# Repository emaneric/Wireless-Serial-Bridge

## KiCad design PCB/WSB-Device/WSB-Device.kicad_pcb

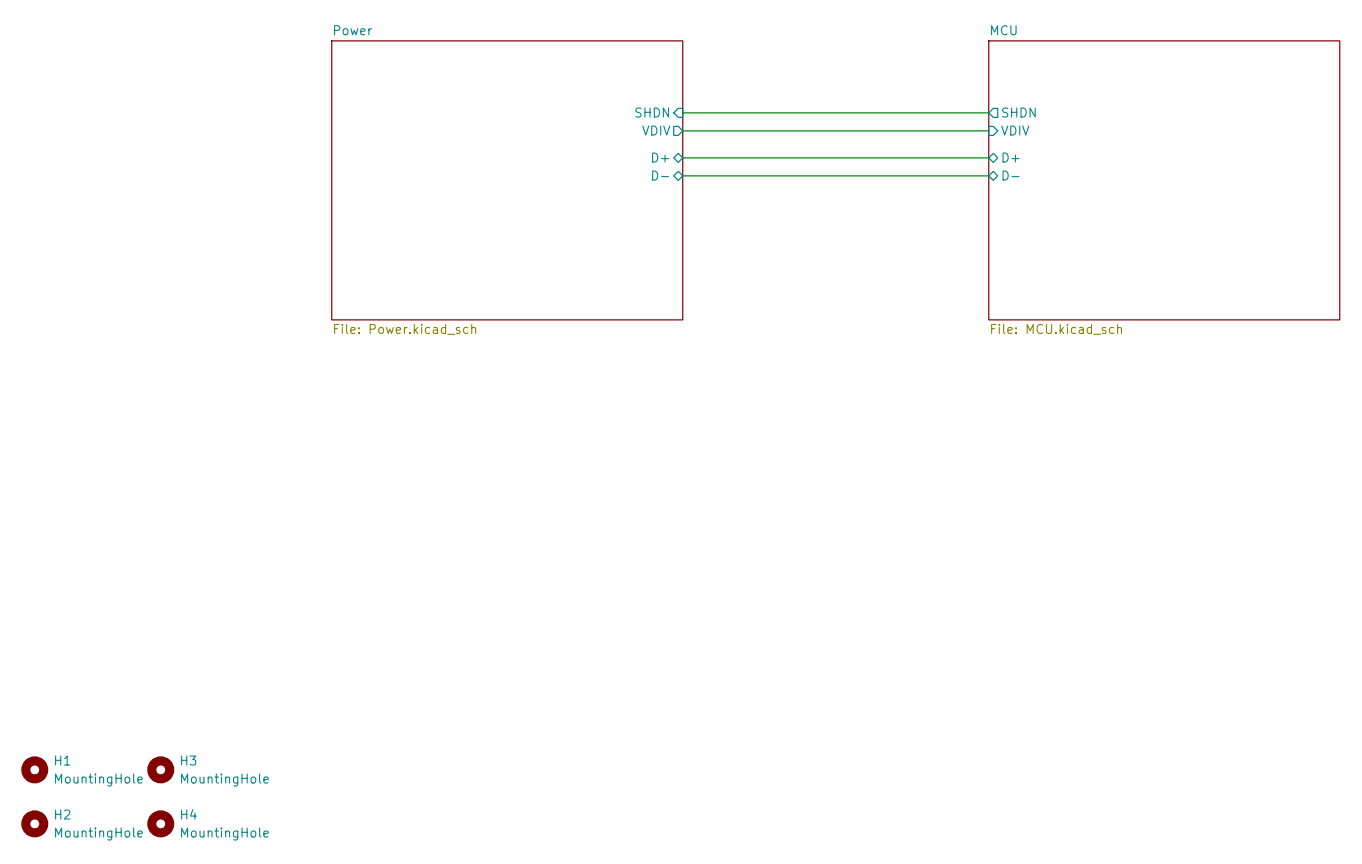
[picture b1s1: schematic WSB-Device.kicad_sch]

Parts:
H1, H2, H3, H4: MountingHole; MountingHole_2.2mm_M2

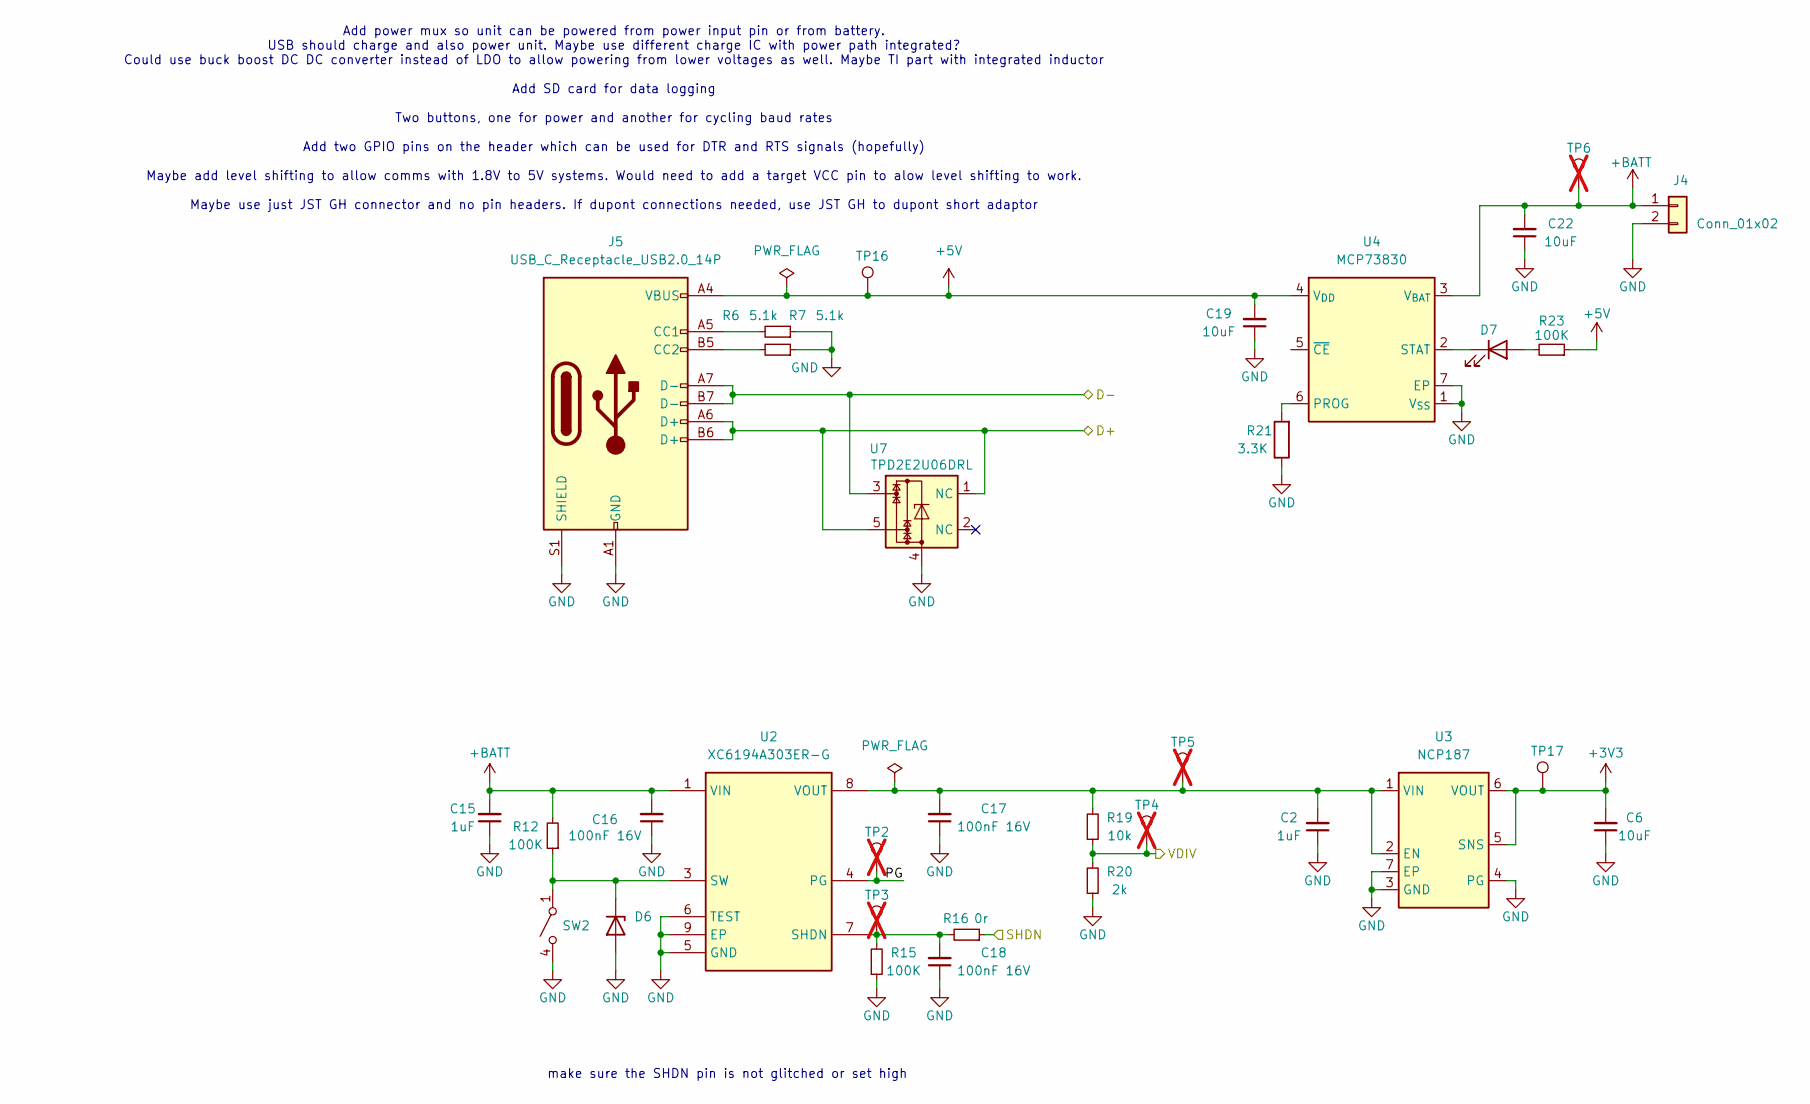
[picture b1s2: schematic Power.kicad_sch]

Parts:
C2: 1uF; C_0402_1005Metric; Voltage 10V
C6, C19, C22: 10uF; C_0603_1608Metric; Voltage 10V
C15: 1uF; C_0603_1608Metric; Voltage 10V
C16, C17, C18: 100nF 16V; C_0402_1005Metric
D6: D_Zener; D_SOD-323
D7: LED; LED_0603_1608Metric
J4: Conn_01x02; JST_PH_S2B-PH-SM4-TB_1x02-1MP_P2.00mm_Horizontal
J5: USB_C_Receptacle_USB2.0_14P; USB_C_Receptacle_G-Switch_GT-USB-7010ASV
R6, R7: 5.1k; R_0201_0603Metric
R12, R15, R23: 100K; R_0402_1005Metric
R16: 0r; R_0402_1005Metric
R19: 10k; R_0402_1005Metric
R20: 2k; R_0402_1005Metric
R21: 3.3K; R_0402_1005Metric
SW2: SW_SPST_4_PIN; 1TS026A-2300-0553-CT
TP2, TP3, TP4, TP5, TP6: TestPoint; TestPoint_Pad_D1.0mm; not fitted
TP16, TP17: TestPoint; TestPoint_Pad_D1.0mm
U2: XC6194A303ER-G; XC6194_USP-8B06
U3: NCP187; OnSemi_WDFN6_2x2_0.65P_CASE_511BR
U4: MCP73830; TDFN-6-1EP_2x2mm_P0.5mm_EP1.6x0.6mm_ThermalVias
U7: TPD2E2U06DRL; SOT-553

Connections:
+3V3: C6.2, TP17.1, U3.5 (SNS), U3.6 (VOUT); also elsewhere on the board
+5V: C19.2, J5.A4 (VBUS), J5.A9 (VBUS), J5.B4 (VBUS), J5.B9 (VBUS), R23.1, TP16.1, U4.4 (V_{DD}); also elsewhere on the board
+BATT: C15.2, C16.2, C22.2, J4.1, R12.2, TP6.1, U2.1 (VIN), U4.3 (V_{BAT})
/MCU/D+: J5.A6 (D+), J5.B6 (D+), U7.1 (NC), U7.5; also elsewhere on the board
/MCU/D-: J5.A7 (D-), J5.B7 (D-), U7.3; also elsewhere on the board
/MCU/SHDN: R16.1; also elsewhere on the board
/MCU/VDIV: R19.1, R20.2, TP4.1; also elsewhere on the board
/Power/PG: TP2.1, U2.4 (PG)
GND: C2.1, C6.1, C15.1, C16.1, C17.1, C18.1, C19.1, C22.1, D6.2 (A), J4.2, J5.A1 (GND), J5.A12 (GND), J5.B1 (GND), J5.B12 (GND), J5.S1 (SHIELD), R6.1, R7.1, R15.1, R20.1, R21.1, SW2.3 (B), SW2.4 (B), U2.5 (GND), U2.6 (TEST), U2.9 (EP), U3.3 (GND), U3.4 (PG), U3.7 (EP), U4.1 (V_{SS}), U4.7 (EP), U7.4; also elsewhere on the board
unnamed: D6.1 (K), R12.1, SW2.1 (A), SW2.2 (A), U2.3 (SW)
unnamed: D7.2 (A), R23.2
unnamed: D7.1 (K), U4.2 (STAT)
unnamed: J5.A5 (CC1), R6.2
unnamed: J5.B5 (CC2), R7.2
unnamed: C18.2, R15.2, R16.2, TP3.1, U2.7 (SHDN)
unnamed: C2.2, C17.2, R19.2, TP5.1, U2.8 (VOUT), U3.1 (VIN), U3.2 (EN)
unnamed: R21.2, U4.6 (PROG)

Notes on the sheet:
Add power mux so unit can be powered from power input pin or from battery. USB should charge and also power unit. Maybe use different charge IC with power path integrated? Could use buck boost DC DC converter instead of LDO to allow powering from lower voltages as well. Maybe TI part with integrate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
make sure the SHDN pin is not glitched or set high

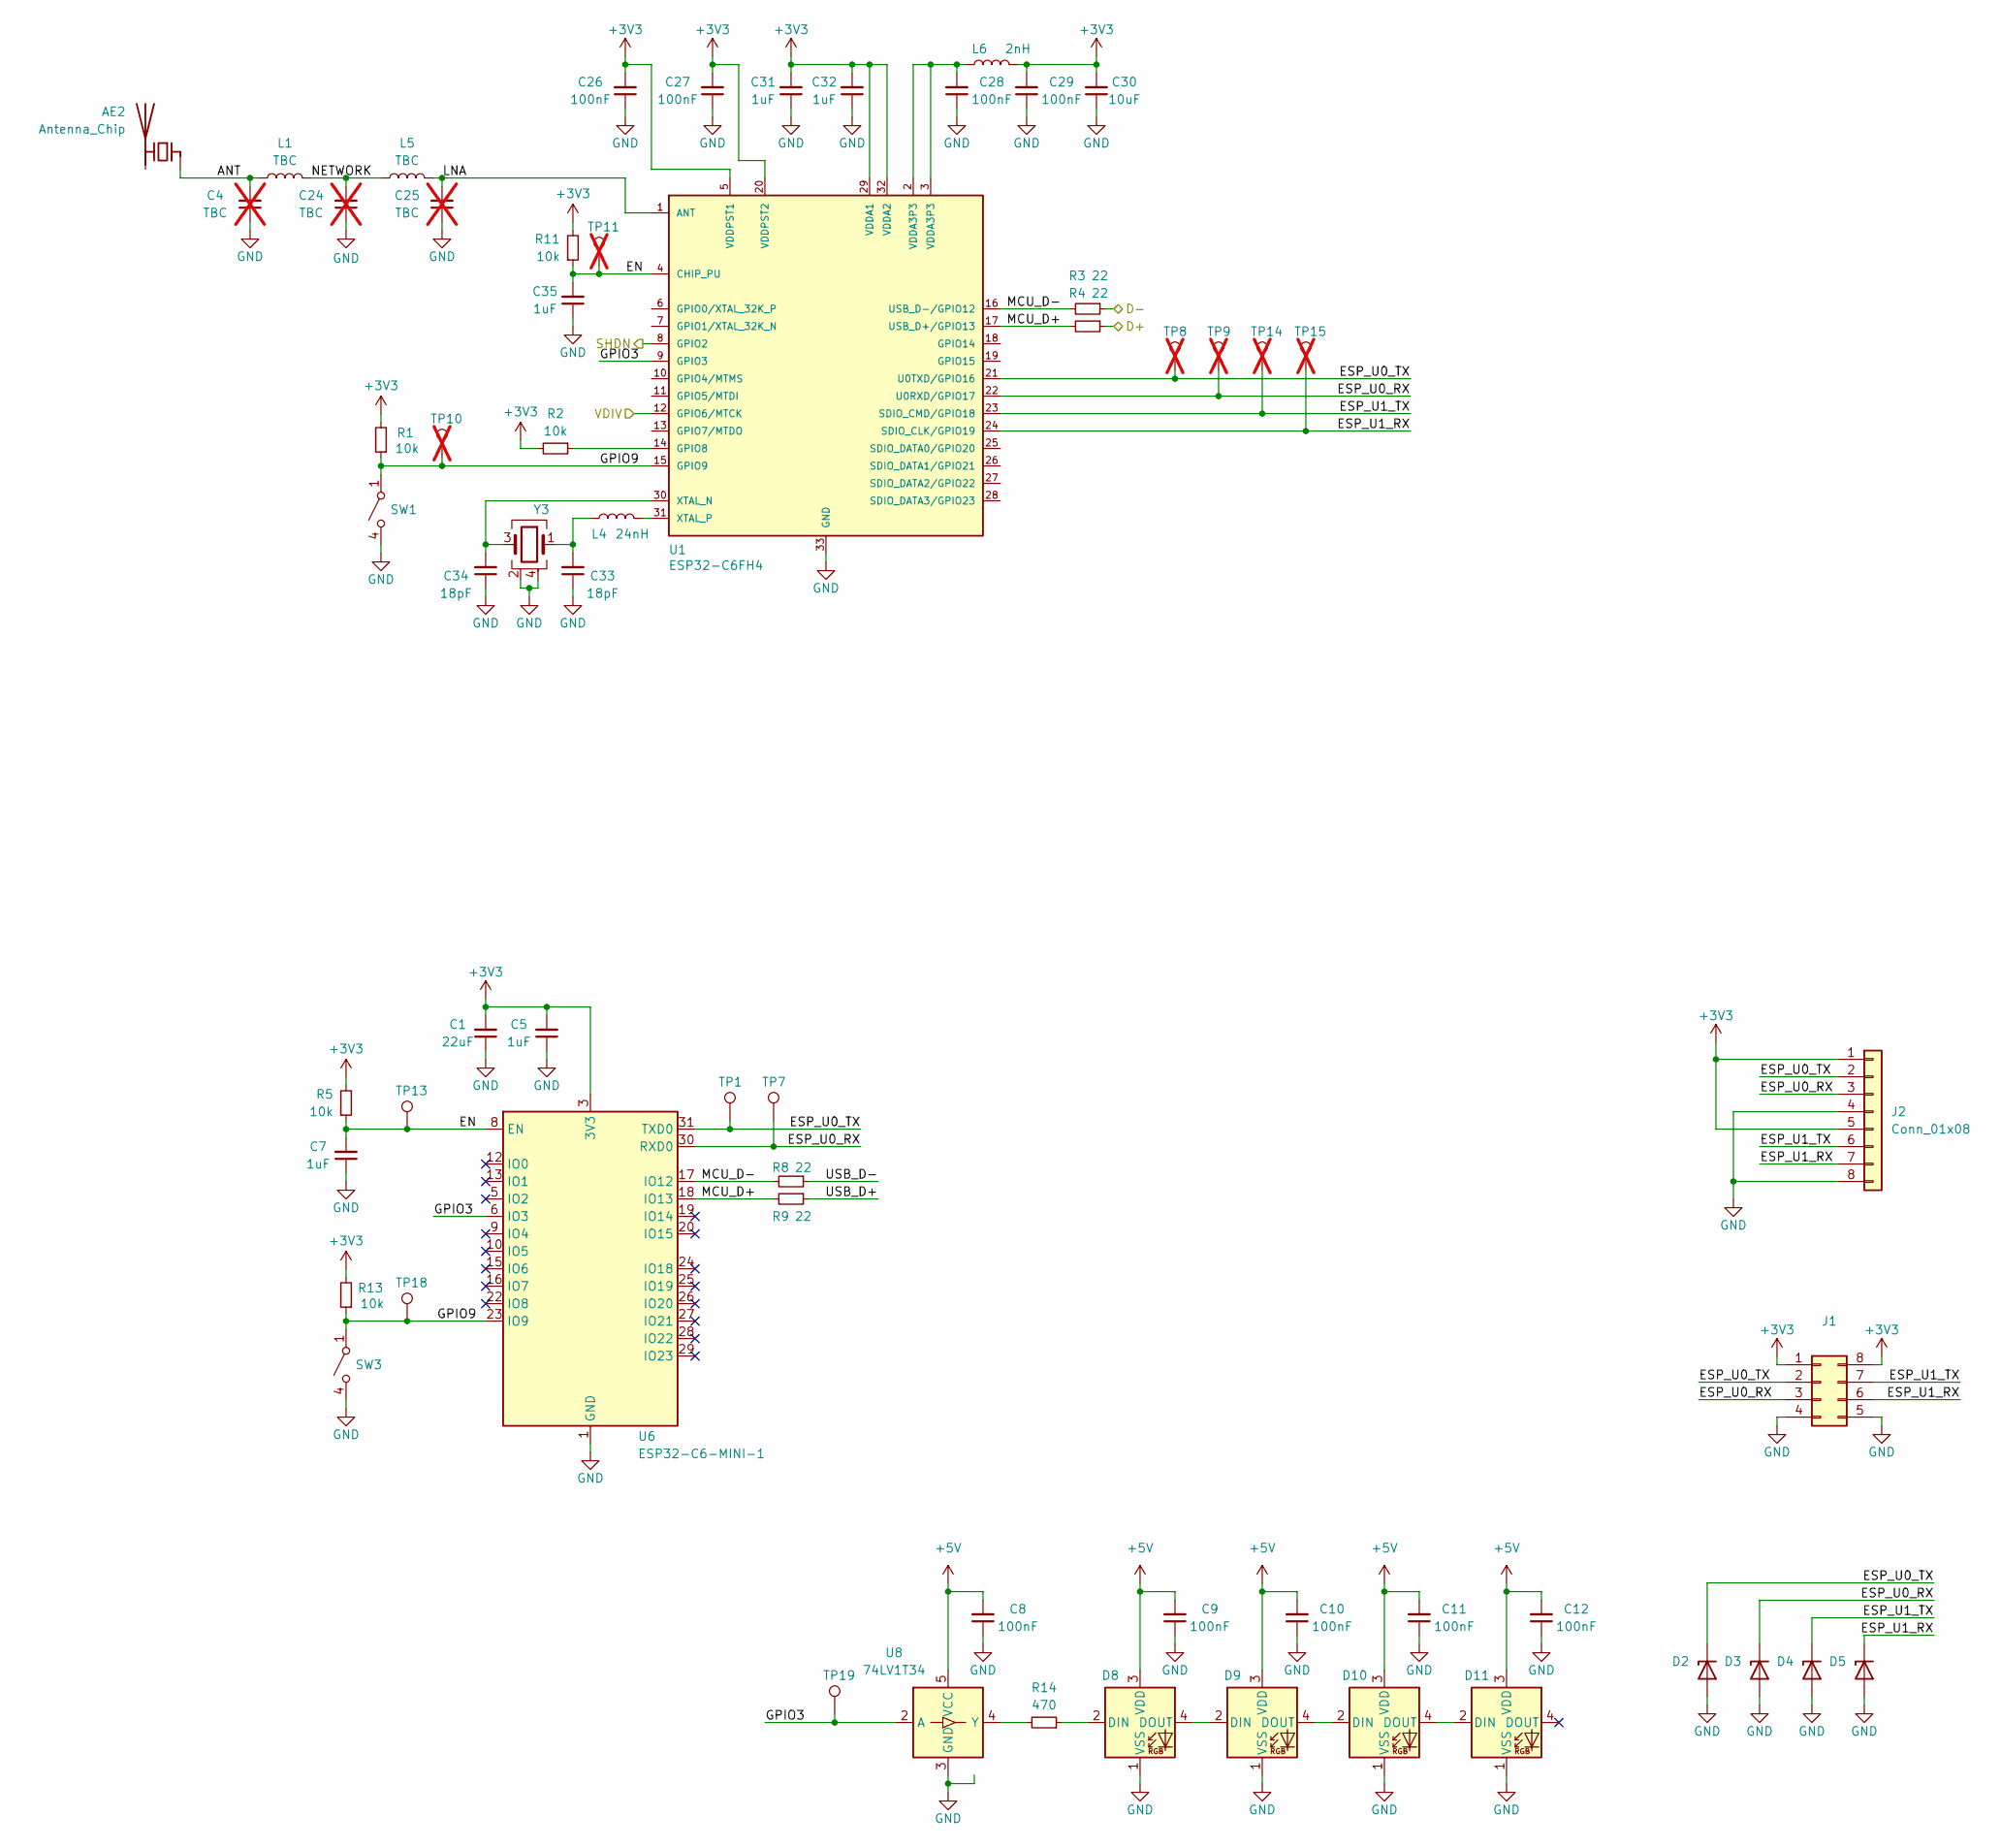
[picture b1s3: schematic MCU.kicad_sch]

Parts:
AE2: Antenna_Chip; ANT3216LL00R2400A
C1: 22uF; C_0603_1608Metric; Voltage 10V
C4, C24, C25: TBC; C_0402_1005Metric; not fitted
C5, C7, C31, C32, C35: 1uF; C_0402_1005Metric; Voltage 10V
C8, C9, C10, C11, C12: 100nF; C_0201_0603Metric; Voltage 10V
C26, C27, C28, C29: 100nF; C_0402_1005Metric; Voltage 10V
C30: 10uF; C_0603_1608Metric; Voltage 10V
C33, C34: 18pF; C_0402_1005Metric; Voltage 10V
D2, D3, D4, D5: ESD7351XV2T1G; D_SOD-323
D8, D9, D10, D11: XL-3210RGBC-2812B
J1: Conn_02x04_Counter_Clockwise; PinHeader_2x04_P2.54mm_Horizontal
J2: Conn_01x08; JST_GH_SM08B-GHS-TB_1x08-1MP_P1.25mm_Horizontal
L1, L5: TBC; L_0402_1005Metric
L4: 24nH; L_0402_1005Metric
L6: 2nH; L_0402_1005Metric
R1, R2, R11: 10k; R_0402_1005Metric
R3, R4: 22; R_0402_1005Metric
R5, R13: 10k; R_0201_0603Metric
R8, R9: 22; R_0201_0603Metric
R14: 470; R_0201_0603Metric
SW1, SW3: SW_SPST_4_PIN; 1TS026A-2300-0553-CT
TP1, TP7, TP13, TP18, TP19: TestPoint; TestPoint_Pad_D1.0mm
TP8, TP9, TP10, TP11, TP14, TP15: TestPoint; TestPoint_Pad_D1.0mm; not fitted
U1: ESP32-C6FH4; QFN-32-1EP_5x5mm_P0.5mm_EP3.7x3.7mm_ThermalVias; PARTREV v0.5
U6: ESP32-C6-MINI-1
U8: 74LV1T34; X2SON5_0.8x0.8mm_SOT1226
Y3: Crystal_GND24; Crystal_SMD_2520-4Pin_2.5x2.0mm

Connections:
+3V3: C1.2, C5.2, C26.2, C27.2, C29.2, C30.2, C31.2, C32.2, J1.1, J1.8, J2.1, J2.5, L6.2, R1.2, R2.2, R5.2, R11.2, R13.2, U1.5 (VDDPST1), U1.20 (VDDPST2), U1.29 (VDDA1), U1.32 (VDDA2), U6.3 (3V3); also elsewhere on the board
+5V: C8.2, C9.2, C10.2, C11.2, C12.2, D8.3 (VDD), D9.3 (VDD), D10.3 (VDD), D11.3 (VDD), U8.5 (VCC); also elsewhere on the board
/MCU/ANT: AE2.1 (FEED), C4.2, L1.1
/MCU/D+: R4.1; also elsewhere on the board
/MCU/D-: R3.1; also elsewhere on the board
/MCU/EN: C7.2, C35.2, R5.1, R11.1, TP11.1, TP13.1, U1.4 (CHIP_PU), U6.8 (EN)
/MCU/ESP_U0_RX: D3.1 (K), J1.3, J2.3, TP7.1, TP9.1, U1.22 (U0RXD/GPIO17), U6.30 (RXD0)
/MCU/ESP_U0_TX: D2.1 (K), J1.2, J2.2, TP1.1, TP8.1, U1.21 (U0TXD/GPIO16), U6.31 (TXD0)
/MCU/ESP_U1_RX: D5.1 (K), J1.6, J2.7, TP15.1, U1.24 (SDIO_CLK/GPIO19)
/MCU/ESP_U1_TX: D4.1 (K), J1.7, J2.6, TP14.1, U1.23 (SDIO_CMD/GPIO18)
/MCU/GPIO3: TP19.1, U1.9 (GPIO3), U6.6 (IO3), U8.2 (A)
/MCU/GPIO9: R1.1, R13.1, SW1.1 (A), SW1.2 (A), SW3.1 (A), SW3.2 (A), TP10.1, TP18.1, U1.15 (GPIO9), U6.23 (IO9)
/MCU/LNA: C25.2, L5.2, U1.1 (ANT)
/MCU/MCU_D+: R4.2, R9.2, U1.17 (USB_D+/GPIO13), U6.18 (IO13)
/MCU/MCU_D-: R3.2, R8.2, U1.16 (USB_D-/GPIO12), U6.17 (IO12)
/MCU/NETWORK: C24.2, L1.2, L5.1
/MCU/SHDN: U1.8 (GPIO2); also elsewhere on the board
/MCU/USB_D+: R9.1
/MCU/USB_D-: R8.1
/MCU/VDIV: U1.12 (GPIO6/MTCK); also elsewhere on the board
GND: C1.1, C4.1, C5.1, C7.1, C8.1, C9.1, C10.1, C11.1, C12.1, C24.1, C25.1, C26.1, C27.1, C28.1, C29.1, C30.1, C31.1, C32.1, C33.1, C34.1, C35.1, D2.2 (A), D3.2 (A), D4.2 (A), D5.2 (A), D8.1 (VSS), D9.1 (VSS), D10.1 (VSS), D11.1 (VSS), J1.4, J1.5, J2.4, J2.8, SW1.3 (B), SW1.4 (B), SW3.3 (B), SW3.4 (B), U1.33 (GND), U6.1 (GND), U6.2 (GND), U6.11 (GND), U6.14 (GND), U6.36 (GND), U6.37 (GND), U6.38 (GND), U6.39 (GND), U6.40 (GND), U6.41 (GND), U6.42 (GND), U6.43 (GND), U6.44 (GND), U6.45 (GND), U6.46 (GND), U6.47 (GND), U6.48 (GND), U6.49 (GND), U6.50 (GND), U6.51 (GND), U6.52 (GND), U6.53 (GND), U8.3 (GND), Y3.2, Y3.4; also elsewhere on the board
unnamed: C28.2, L6.1, U1.2 (VDDA3P3), U1.3 (VDDA3P3)
unnamed: C33.2, L4.2, Y3.1
unnamed: D8.2 (DIN), R14.1
unnamed: D8.4 (DOUT), D9.2 (DIN)
unnamed: D9.4 (DOUT), D10.2 (DIN)
unnamed: D10.4 (DOUT), D11.2 (DIN)
unnamed: R2.1, U1.14 (GPIO8)
unnamed: C34.2, U1.30 (XTAL_N), Y3.3
unnamed: L4.1, U1.31 (XTAL_P)
unnamed: R14.2, U8.4 (Y)

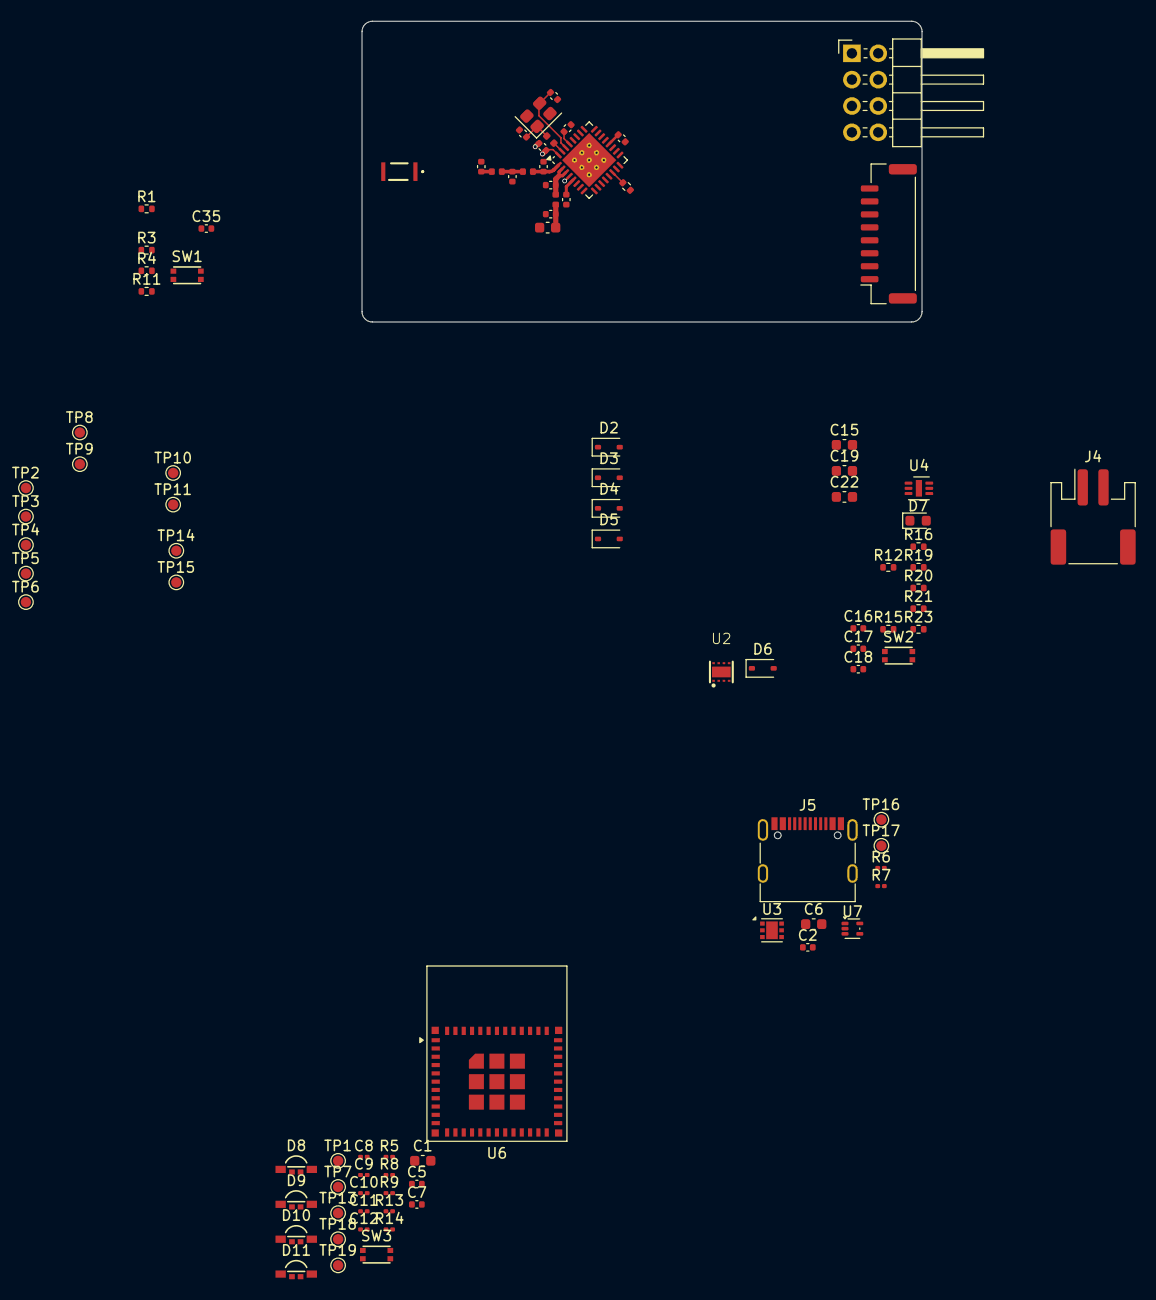
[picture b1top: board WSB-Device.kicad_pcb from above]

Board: 4 copper layers, 54.0 x 29.0 mm, 99 parts (0 on the bottom side), 38 nets.

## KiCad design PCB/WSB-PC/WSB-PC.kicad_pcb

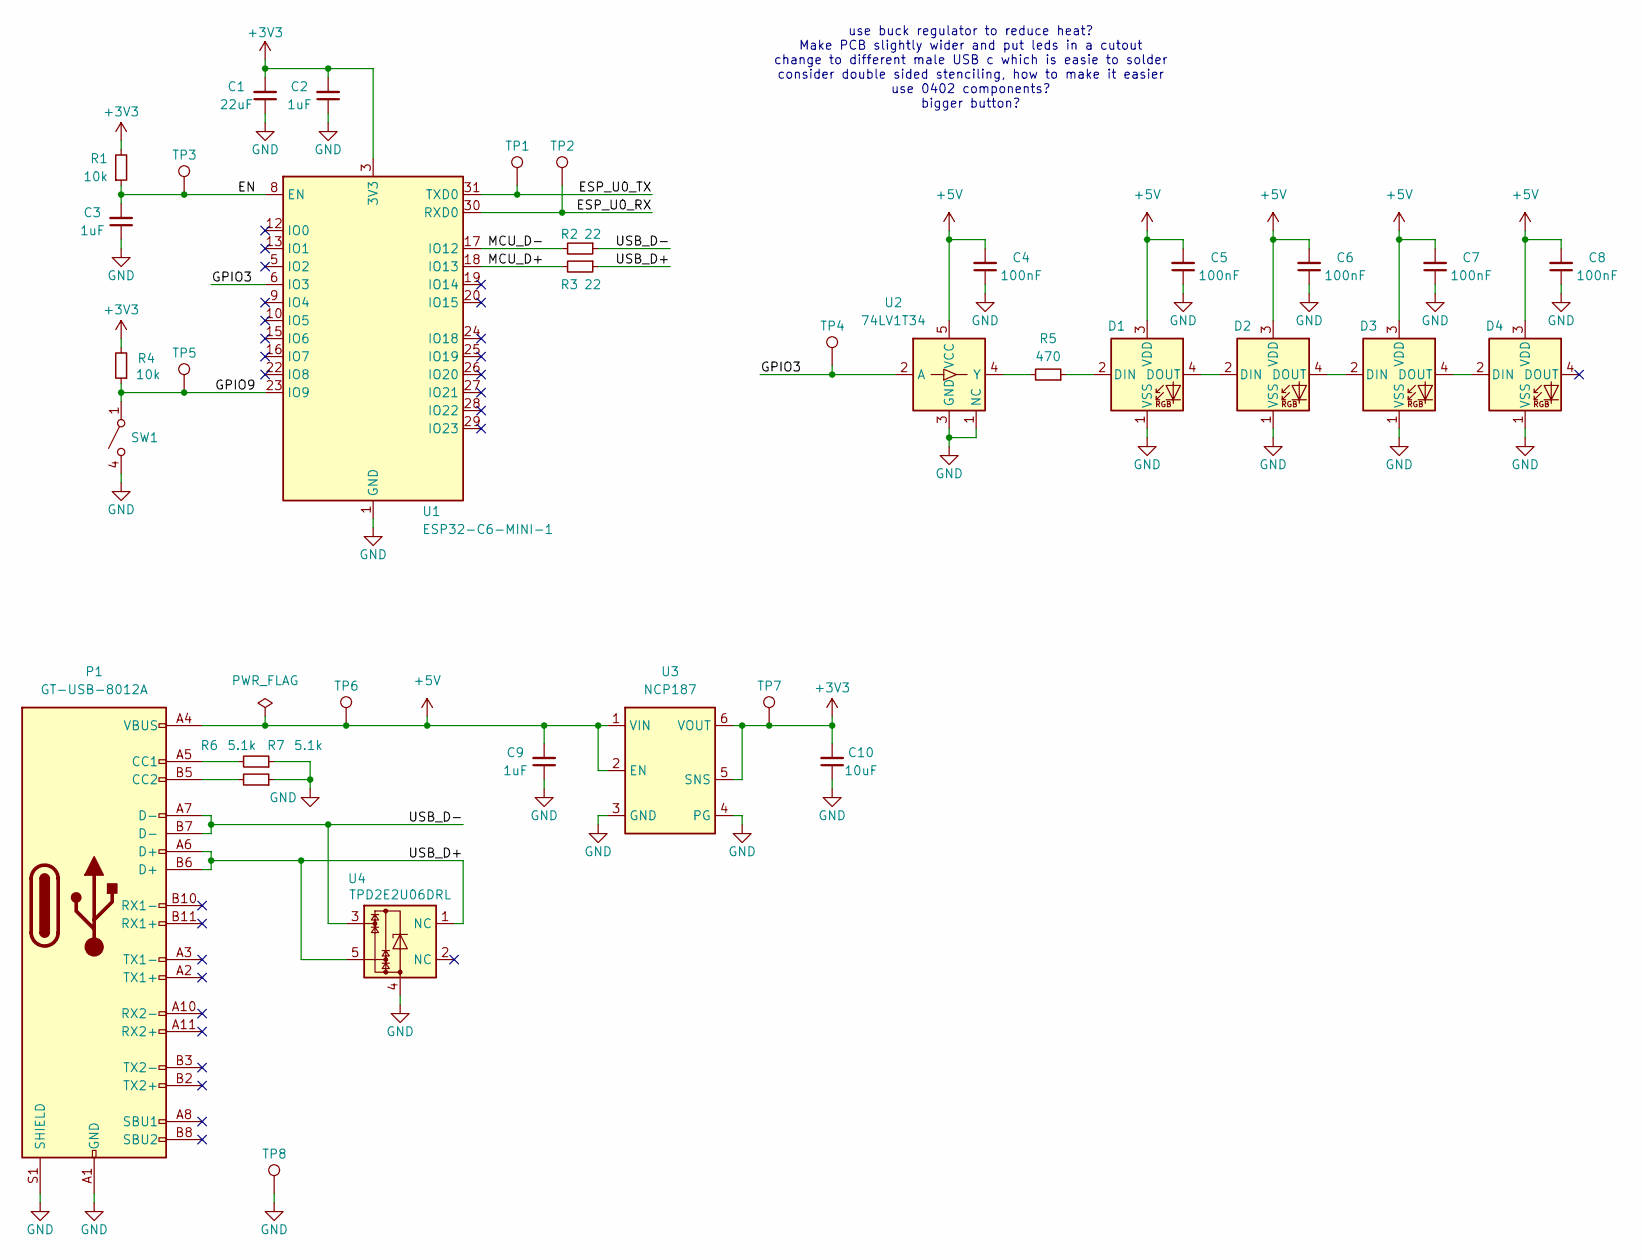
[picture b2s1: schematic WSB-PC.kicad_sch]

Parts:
C1: 22uF; C_0603_1608Metric; Voltage 10V
C2, C3, C9: 1uF; C_0402_1005Metric; Voltage 10V
C4, C5, C6, C7, C8: 100nF; C_0201_0603Metric; Voltage 10V
C10: 10uF; C_0603_1608Metric; Voltage 10V
D1, D2, D3, D4: XL-3210RGBC-2812B
P1: GT-USB-8012A
R1, R4: 10k; R_0201_0603Metric
R2, R3: 22; R_0201_0603Metric
R5: 470; R_0201_0603Metric
R6, R7: 5.1k; R_0201_0603Metric
SW1: SW_SPST_4_PIN; 1TS026A-2300-0553-CT
TP1, TP2, TP3, TP4, TP5, TP6, TP7, TP8: TestPoint; TestPoint_Pad_D1.0mm
U1: ESP32-C6-MINI-1
U2: 74LV1T34; X2SON5_0.8x0.8mm_SOT1226
U3: NCP187; OnSemi_WDFN6_2x2_0.65P_CASE_511BR
U4: TPD2E2U06DRL; SOT-553

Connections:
+3V3: C1.2, C2.2, C10.2, R1.2, R4.2, TP7.1, U1.3 (3V3), U3.5 (SNS), U3.6 (VOUT)
+5V: C4.2, C5.2, C6.2, C7.2, C8.2, C9.2, D1.3 (VDD), D2.3 (VDD), D3.3 (VDD), D4.3 (VDD), P1.A4 (VBUS), P1.A9 (VBUS), P1.B4 (VBUS), P1.B9 (VBUS), TP6.1, U2.5 (VCC), U3.1 (VIN), U3.2 (EN)
/EN: C3.2, R1.1, TP3.1, U1.8 (EN)
/ESP_U0_RX: TP2.1, U1.30 (RXD0)
/ESP_U0_TX: TP1.1, U1.31 (TXD0)
/GPIO3: TP4.1, U1.6 (IO3), U2.2 (A)
/GPIO9: R4.1, SW1.1 (A), SW1.2 (A), TP5.1, U1.23 (IO9)
/MCU_D+: R3.2, U1.18 (IO13)
/MCU_D-: R2.2, U1.17 (IO12)
/USB_D+: P1.A6 (D+), P1.B6 (D+), R3.1, U4.1 (NC), U4.5
/USB_D-: P1.A7 (D-), P1.B7 (D-), R2.1, U4.3
GND: C1.1, C2.1, C3.1, C4.1, C5.1, C6.1, C7.1, C8.1, C9.1, C10.1, D1.1 (VSS), D2.1 (VSS), D3.1 (VSS), D4.1 (VSS), P1.A1 (GND), P1.A12 (GND), P1.B1 (GND), P1.B12 (GND), P1.S1 (SHIELD), R6.1, R7.1, SW1.3 (B), SW1.4 (B), TP8.1, U1.1 (GND), U1.2 (GND), U1.11 (GND), U1.14 (GND), U1.36 (GND), U1.37 (GND), U1.38 (GND), U1.39 (GND), U1.40 (GND), U1.41 (GND), U1.42 (GND), U1.43 (GND), U1.44 (GND), U1.45 (GND), U1.46 (GND), U1.47 (GND), U1.48 (GND), U1.49 (GND), U1.50 (GND), U1.51 (GND), U1.52 (GND), U1.53 (GND), U2.1 (NC), U2.3 (GND), U3.3 (GND), U3.4 (PG), U3.7 (EP), U4.4
unnamed: D1.2 (DIN), R5.1
unnamed: D1.4 (DOUT), D2.2 (DIN)
unnamed: D2.4 (DOUT), D3.2 (DIN)
unnamed: D3.4 (DOUT), D4.2 (DIN)
unnamed: P1.A5 (CC1), R6.2
unnamed: P1.B5 (CC2), R7.2
unnamed: R5.2, U2.4 (Y)

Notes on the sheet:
use buck regulator to reduce heat? Make PCB slightly wider and put leds in a cutout change to different male USB c which is easie to solder consider double sided stenciling, how to make it easier use 0402 components? bigger button?

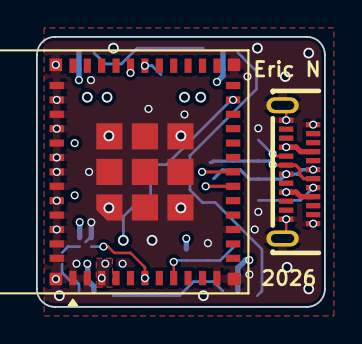
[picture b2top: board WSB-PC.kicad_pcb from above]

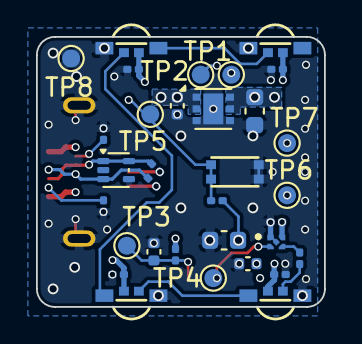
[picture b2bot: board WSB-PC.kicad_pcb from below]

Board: 6 copper layers, 16.0 x 15.0 mm, 35 parts (33 on the bottom side), 19 nets.

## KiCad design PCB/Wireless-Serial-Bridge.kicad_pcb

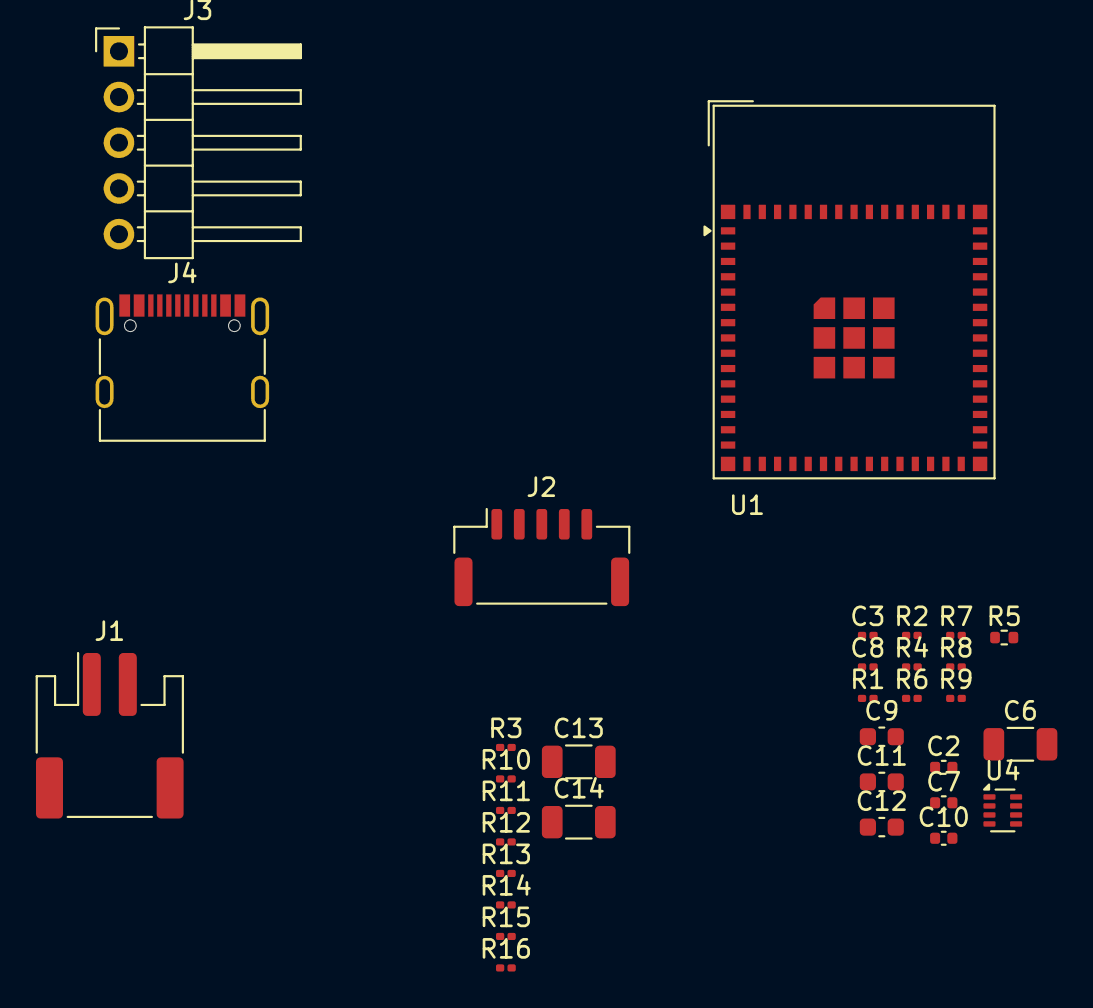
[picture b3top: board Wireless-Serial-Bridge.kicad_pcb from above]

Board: 2 copper layers, 33 parts (0 on the bottom side), 17 nets, no tracks yet.

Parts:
C2, C10: 1uF; C_0402_1005Metric
C3, C8: 100nF 16V; C_0201_0603Metric
C6: 22uF; C_1206_3216Metric
C7: 100nF; C_0402_1005Metric
C9, C11, C12: 1uF; C_0603_1608Metric
C13, C14: 10uF; C_1206_3216Metric
J1: Conn_01x02; JST_PH_S2B-PH-SM4-TB_1x02-1MP_P2.00mm_Horizontal
J2: Conn_01x05; JST_GH_SM05B-GHS-TB_1x05-1MP_P1.25mm_Horizontal
J3: Conn_01x05; PinHeader_1x05_P2.54mm_Horizontal
J4: USB_C_Receptacle_USB2.0_14P; USB_C_Receptacle_G-Switch_GT-USB-7010ASV
R1, R2, R3, R4, R10, R11, R12, R16: 100K; R_0201_0603Metric
R5: 10k; R_0402_1005Metric
R6: 2.8k; R_0201_0603Metric
R7, R14: 10k; R_0201_0603Metric
R8, R9: 5.1k; R_0201_0603Metric
R13: 6.8; R_0201_0603Metric
R15: 3.3K; R_0201_0603Metric
U1: ESP32-S3-MINI-1; ESP32-S2-MINI-1
U4: TPS2116DRL; SOT-583-8

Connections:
+3V3: C6.2, C7.2, C10.2, R3.2, R5.2, R16.2, U1.3 (3V3)
+5V: C11.2, C14.2, J4.A4 (VBUS), J4.A9 (VBUS), J4.B4 (VBUS), J4.B9 (VBUS), R7.2, U4.3 (VIN1), U4.5 (MODE)
+BATT: C12.2, C13.2, J1.1, U4.6 (VIN2)
/D+: J4.A6 (D+), J4.B6 (D+), U1.24 (IO20)
/D-: J4.A7 (D-), J4.B7 (D-), U1.23 (IO19)
/EN: C9.2, R5.1, U1.45 (EN)
/EXT_RX: J2.2, J3.2, U1.21 (IO17)
/EXT_TX: J2.3, J3.3, U1.22 (IO18)
/VDIV: R13.1, R14.2
GND: C2.1, C3.1, C6.1, C7.1, C8.1, C9.1, C10.1, C11.1, C12.1, C13.1, C14.1, J1.2, J2.4, J2.5, J3.4, J3.5, J4.A1 (GND), J4.A12 (GND), J4.B1 (GND), J4.B12 (GND), J4.S1 (SHIELD), R1.1, R4.1, R6.1, R8.1, R9.1, R14.1, R15.1, U1.1 (GND), U1.2 (GND), U1.42 (GND), U1.43 (GND), U1.46 (GND), U1.47 (GND), U1.48 (GND), U1.49 (GND), U1.50 (GND), U1.51 (GND), U1.52 (GND), U1.53 (GND), U1.54 (GND), U1.55 (GND), U1.56 (GND), U1.57 (GND), U1.58 (GND), U1.59 (GND), U1.60 (GND), U1.61 (GND), U1.62 (GND), U1.63 (GND), U1.64 (GND), U1.65 (GND), U4.1 (GND)
unnamed: J2.1, J3.1
unnamed: J4.A5 (CC1), R9.2
unnamed: J4.B5 (CC2), R8.2
unnamed: C2.2, C8.2, R13.2
unnamed: R6.2, R7.1, U4.4 (PR1)
unnamed: R1.2, U4.8 (ST)
unnamed: C3.2, R2.2, U4.2 (VOUT), U4.7 (VOUT)

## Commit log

2024-11-03 Schematic design in progress
2024-11-03 Work in progress
2026-02-06 -Completed ESP32 C6 PC device
2026-03-28 -Corrected test point numbering
2026-03-28 -Changed USB connector -Moved LEDs in behind board edge -Changed to smaller test points
